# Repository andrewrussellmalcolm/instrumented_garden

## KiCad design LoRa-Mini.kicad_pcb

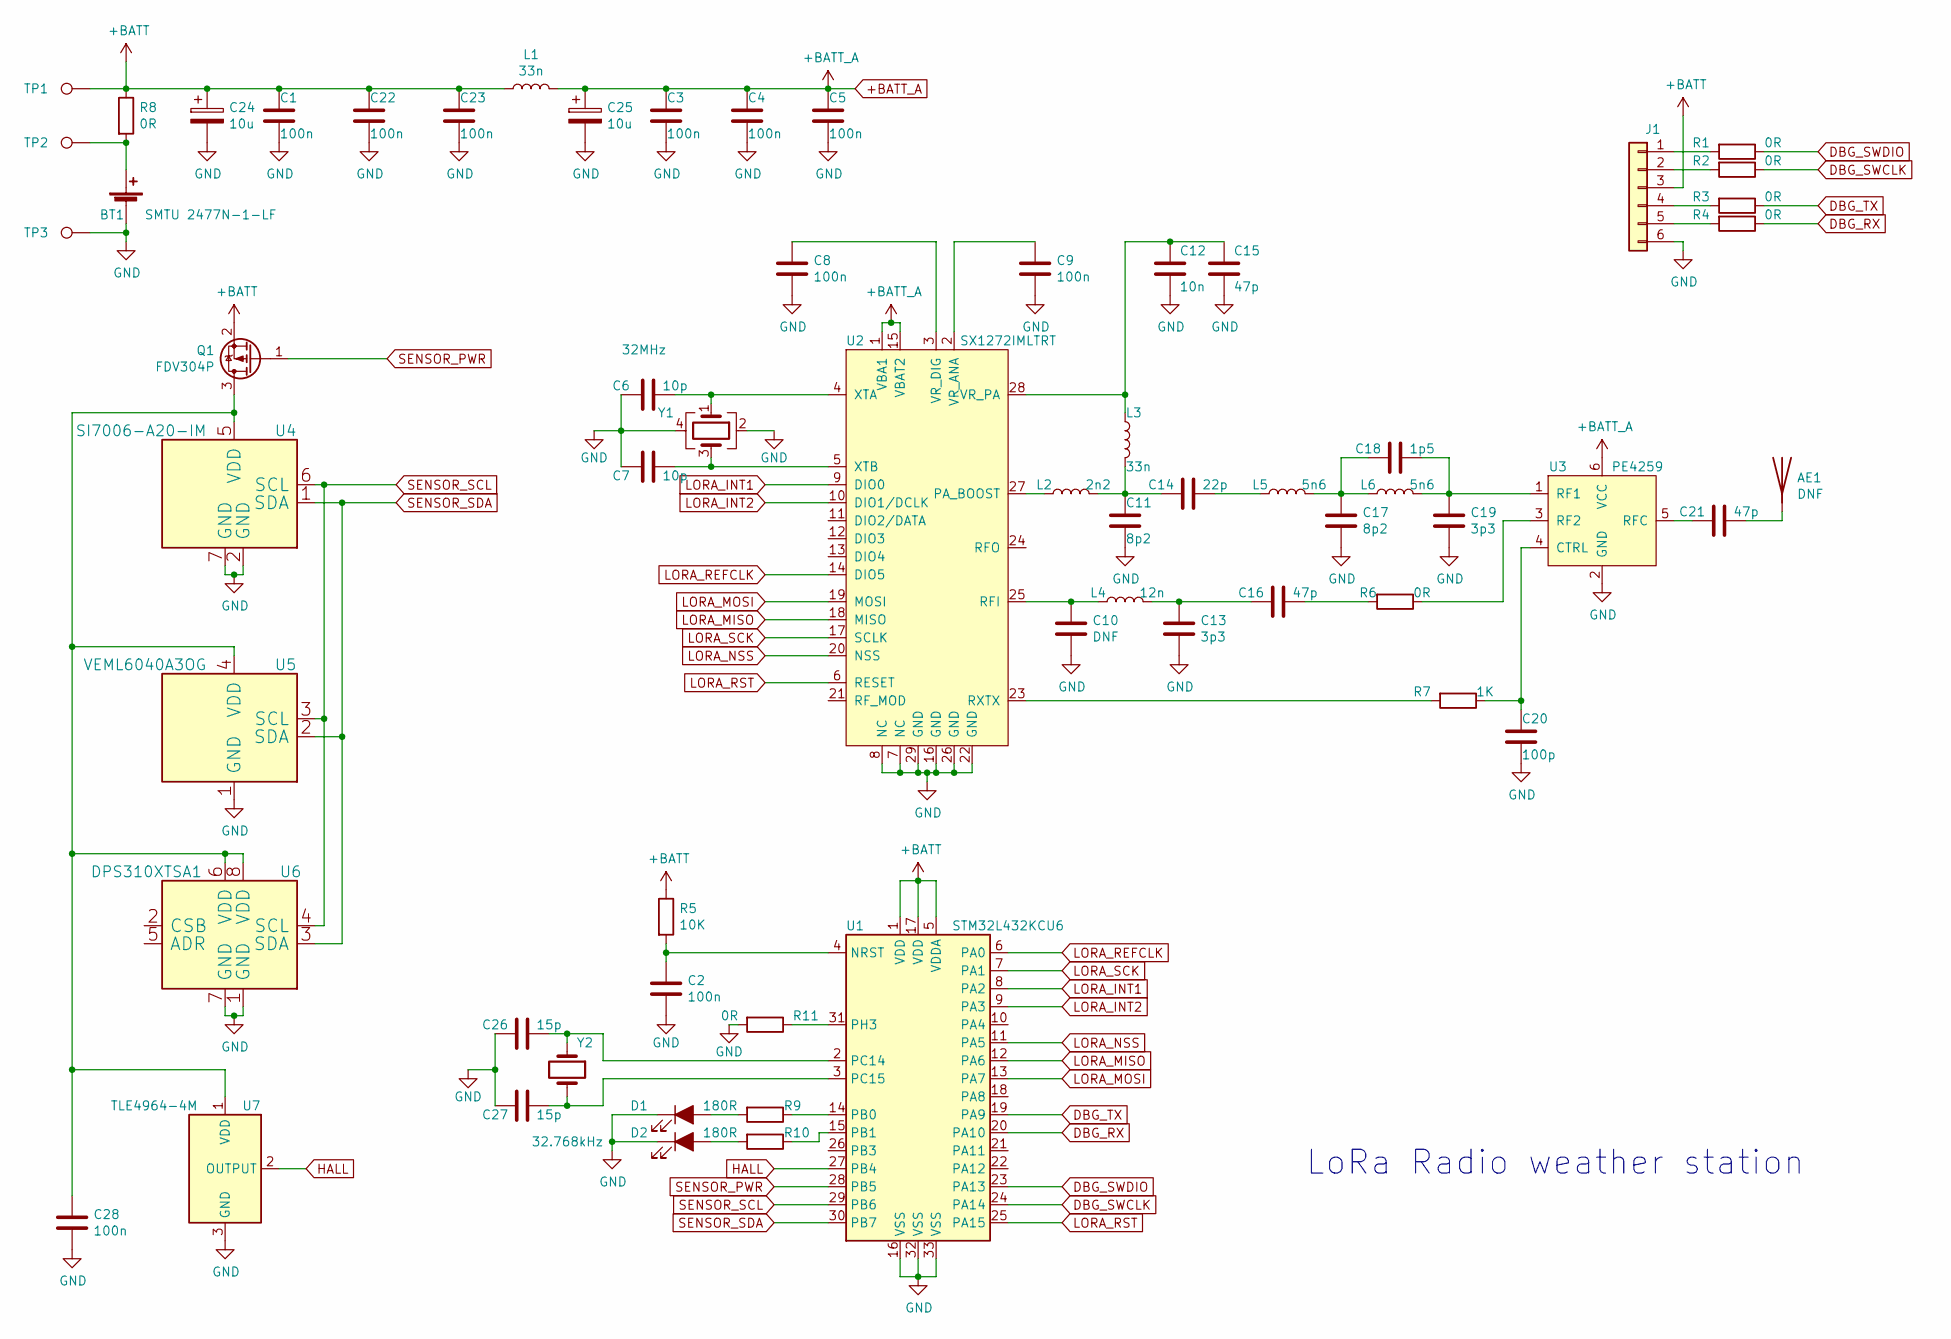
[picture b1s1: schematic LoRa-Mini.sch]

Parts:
AE1: DNF; SPRING_ANTENNA_868MHz
BT1: SMTU 2477N-1-LF; BatteryHolder_SMTU2477N-LF
C1, C3, C4, C5, C8, C9, C22, C23, C28: 100n; C_0603_1608Metric; Voltage 50V; PartNo C0603C104K3RACTU
C2: 100n; C_0603_1608Metric; Voltage 50V
C6, C7: 10p; C_0603_1608Metric; Voltage 50V; PartNo C0603C150J5GACTU
C10: DNF; C_0603_1608Metric
C11, C17: 8p2; C_0603_1608Metric; Voltage 50V; PartNo C0603C829C5GACTU
C12: 10n; C_0603_1608Metric; Voltage 50V; PartNo C0603C103K5RACTU
C13, C19: 3p3; C_0603_1608Metric; Voltage 50V; PartNo C0603C339C5GACTU
C14: 22p; C_0603_1608Metric; Voltage 50V; PartNo C0603C220J5GACTU
C15, C16, C21: 47p; C_0603_1608Metric; Voltage 50V; PartNo C0603C470J5GACTU
C18: 1p5; C_0603_1608Metric; Voltage 50V; PartNo C0603C159C1GACTU
C20: 100p; C_0603_1608Metric; Voltage 50V; PartNo C0603C101J5GACTU
C24, C25: 10u; CP_EIA-3216-10_Kemet-I; Voltage 6.3V
C26, C27: 15p; C_0603_1608Metric; Voltage 50V; PartNo C0603C150J5GACTU
D1: LTST-C190KRKT; D_0603_1608Metric
D2: LTST-C190KGKT; D_0603_1608Metric
J1: Conn_01x06; PinHeader_1x06_P2.54mm_Vertical
L1, L3: 33n; L_0603_1608Metric; PartNo LQW18AN33NJ10D
L2: 2n2; L_0603_1608Metric; PartNo LQW18AN2N2D10D
L4: 12n; L_0603_1608Metric; PartNo LQW18AN12NG10D
L5, L6: 5n6; L_0603_1608Metric; PartNo LQW18AN5N6D10D
Q1: FDV304P; SOT-23
R1, R2, R3, R4, R8, R11: 0R; R_0603_1608Metric
R5: 10K; R_0603_1608Metric
R6: 0R; R_0603_1608Metric; PartNo CRG0603ZR
R7: 1K; R_0603_1608Metric; PartNo CRG0603F1K0
R9, R10: 180R; R_0603_1608Metric
TP1, TP2, TP3: DNF; TestPoint_Pad_D2.0mm
U1: STM32L432KCU6; QFN-32-1EP_5x5mm_P0.5mm_EP3.45x3.45mm
U2: SX1272IMLTRT; QFN-28-1EP_6x6mm_P0.65mm_EP4.8x4.8mm_ThermalVias
U3: PE4259; SOT-363_SC-70-6
U4: SI7006-A20-IM; DFN-6-1EP_3x3mm_P1mm_EP1.5x2.4mm
U5: VEML6040A3OG; OPLGA
U6: DPS310XTSA1; PG-VGA-8-1
U7: TLE4964-4M; SOT-23
Y1: 32MHz; Crystal_SMD_2016-4Pin_2.0x1.6mm; PartNo Q22FA1280002511
Y2: 32.768kHz; Crystal_SMD_MicroCrystal_CC8V-T1A-2Pin_2.0x1.2mm_HandSolder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

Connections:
+BATT: C1.1, C22.1, C23.1, C24.1, J1.3, L1.1, Q1.2 (S), R5.1, R8.1, TP1.1, U1.1 (VDD), U1.5 (VDDA), U1.17 (VDD)
+BATT_A: C3.1, C4.1, C5.1, C25.1, L1.2, U2.1 (VBA1), U2.15 (VBAT2), U3.6 (VCC)
DBG_RX: R4.1, U1.20 (PA10)
DBG_SWCLK: R2.1, U1.24 (PA14)
DBG_SWDIO: R1.1, U1.23 (PA13)
DBG_TX: R3.1, U1.19 (PA9)
GND: BT1.2 (-), C1.2, C2.2, C3.2, C4.2, C5.2, C6.2, C7.2, C8.2, C9.2, C10.2, C11.2, C12.2, C13.2, C15.2, C17.2, C19.2, C20.2, C22.2, C23.2, C24.2, C25.2, C26.2, C27.2, C28.2, D1.1 (K), D2.1 (K), J1.6, R11.2, TP3.1, U1.16 (VSS), U1.32 (VSS), U1.33 (VSS), U2.7 (NC), U2.8 (NC), U2.16 (GND), U2.22 (GND), U2.26 (GND), U2.29 (GND), U3.2 (GND), U4.2 (GND), U4.7 (GND), U5.1 (GND), U6.1 (GND), U6.7 (GND), U7.3 (GND), Y1.2, Y1.4
HALL: U1.27 (PB4), U7.2 (OUTPUT)
LORA_INT1: U1.8 (PA2), U2.9 (DIO0)
LORA_INT2: U1.9 (PA3), U2.10 (DIO1/DCLK)
LORA_MISO: U1.12 (PA6), U2.18 (MISO)
LORA_MOSI: U1.13 (PA7), U2.19 (MOSI)
LORA_NSS: U1.11 (PA5), U2.20 (NSS)
LORA_REFCLK: U1.6 (PA0), U2.14 (DIO5)
LORA_RST: U1.25 (PA15), U2.6 (RESET)
LORA_SCK: U1.7 (PA1), U2.17 (SCLK)
unnamed: AE1.1, C21.1
unnamed: BT1.1 (+), R8.2, TP2.1
unnamed: C2.1, R5.2, U1.4 (NRST)
unnamed: C6.1, U2.4 (XTA), Y1.1
unnamed: C7.1, U2.5 (XTB), Y1.3
unnamed: C8.1, U2.3 (VR_DIG)
unnamed: C9.1, U2.2 (VR_ANA)
unnamed: C10.1, L4.1, U2.25 (RFI)
unnamed: C11.1, C14.2, L2.2, L3.2
unnamed: C12.1, C15.1, L3.1, U2.28 (VR_PA)
unnamed: C13.1, C16.2, L4.2
unnamed: C14.1, L5.1
unnamed: C16.1, R6.2
unnamed: C17.1, C18.2, L5.2, L6.1
unnamed: C18.1, C19.1, L6.2, U3.1 (RF1)
unnamed: C20.1, R7.1, U3.4 (CTRL)
unnamed: C21.2, U3.5 (RFC)
unnamed: C26.1, U1.2 (PC14), Y2.1
unnamed: C27.1, U1.3 (PC15), Y2.2
unnamed: C28.1, Q1.3 (D), U4.5 (VDD), U5.4 (VDD), U6.6 (VDD), U6.8 (VDD), U7.1 (VDD)
unnamed: D1.2 (A), R9.2
unnamed: D2.2 (A), R10.2
unnamed: J1.1, R1.2
unnamed: J1.2, R2.2
unnamed: J1.4, R3.2
unnamed: J1.5, R4.2
unnamed: L2.1, U2.27 (PA_BOOST)
unnamed: R6.1, U3.3 (RF2)
unnamed: R7.2, U2.23 (RXTX)
unnamed: R9.1, U1.14 (PB0)
unnamed: R10.1, U1.15 (PB1)
unnamed: R11.1, U1.31 (PH3)
SENSOR_PWR: Q1.1 (G), U1.28 (PB5)
SENSOR_SCL: U1.29 (PB6), U4.6 (SCL), U5.3 (SCL), U6.4 (SCL)
SENSOR_SDA: U1.30 (PB7), U4.1 (SDA), U5.2 (SDA), U6.3 (SDA)

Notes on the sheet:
LoRa Radio weather station

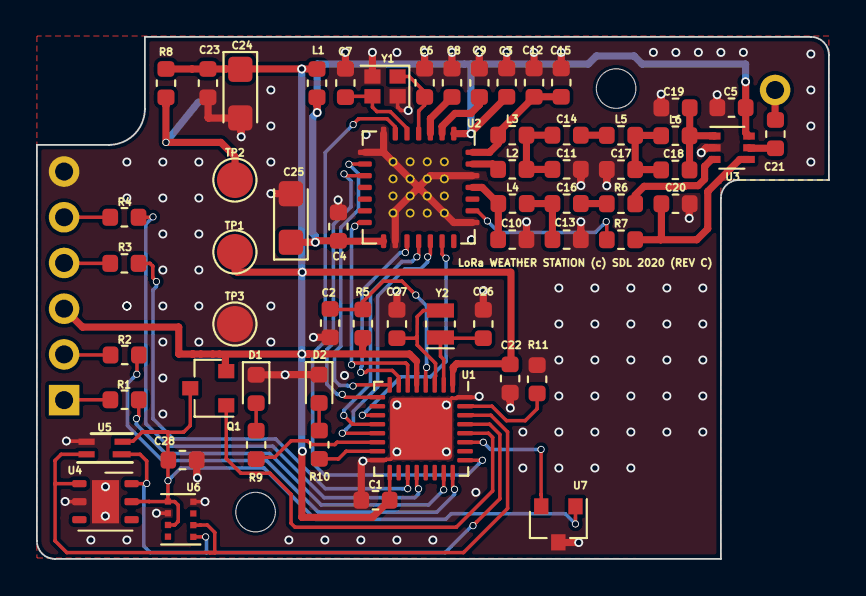
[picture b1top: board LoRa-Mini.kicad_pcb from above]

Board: 2 copper layers, 44.0 x 29.0 mm, 65 parts (0 on the bottom side), 51 nets.

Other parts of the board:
MOUNTING_HOLE 2.2mm, MOUNTING_HOLE 2.2mm#2: VAL**; MOUNTING_HOLE_2.2mm
